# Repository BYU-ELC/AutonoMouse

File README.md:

# AutonoMouse

## Introduction
Lightweight and low cost autonomous robotics platform for students to gain skills and have fun!

There are two version to this project. 

V1's objective is to build a small autonomous car using Arduino Nano as a controller. The car drives forward until sensing an object. When it senses an object it pivots to both sides to find both distances to the nearest object. It then chooses to travel the distance that is greater. 

V2's objective is to build a similiar autonomous car using ESP32 as a controller. However, this version
allow's the user to put the car into remote control mode where the user can control the car via bluetooth
using an Android smartphone. This doesn't work with an IPhone because there are no opensource bluetooth apps 
that in the App Store. 

## V1 Things to Change
More accessibility Linux and Apple users. Document how to download Arduino IDE and how to interfaces with Arduino devices.

## V2 Things to Change
Finish development for V2. Mostly needs work with the servos.

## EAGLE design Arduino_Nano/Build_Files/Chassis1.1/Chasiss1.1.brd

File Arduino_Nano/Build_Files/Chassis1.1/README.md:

Chassis1.1 is a revision of the previous Chassis1.0.

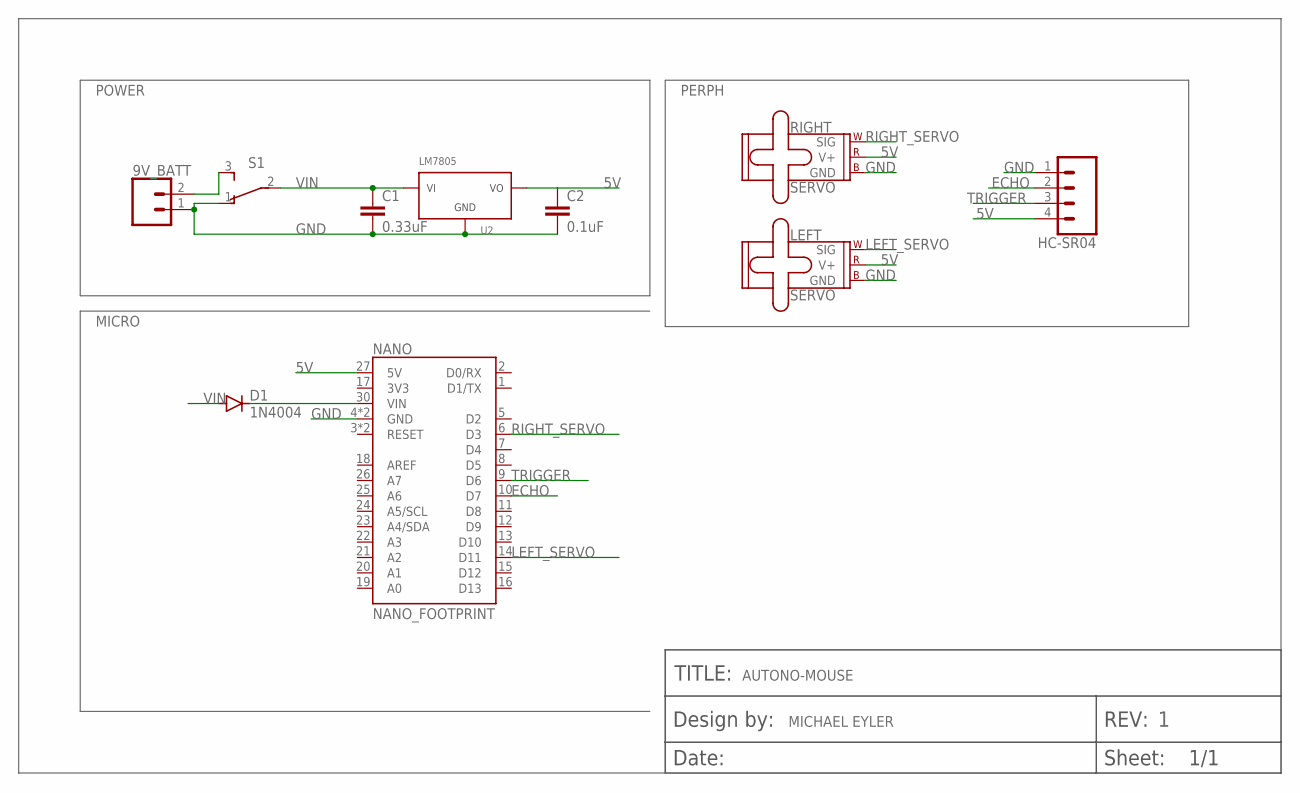
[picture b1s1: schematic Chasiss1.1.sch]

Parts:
9V_BATT: CONN_02; 1X02
C1: 0.33uF; CAP-PTH-SMALL-KIT
C2: 0.1uF; CAP-PTH-SMALL-KIT
D1: 1N4004; DO41-10
HC-SR04: CONN_04PTH; 1X04
LEFT: SERVO; 1X03
NANO: NANO_FOOTPRINT; NANO
RIGHT: SERVO; 1X03
S1: TL36PO; TL3XPO
U2: LM7805; TO220H
U$1: FRAME-BADGE; DUMMY

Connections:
5V: C2.1, HC-SR04.4, LEFT.2 (V+), NANO.27 (5V), RIGHT.2 (V+), U2.3 (VOUT)
ECHO: HC-SR04.2, NANO.10 (D7)
GND: 9V_BATT.1, C1.2, C2.2, HC-SR04.1, LEFT.3 (GND), NANO.4 (GND), NANO.29 (GND), RIGHT.3 (GND), S1.1 (O), U2.2 (GND)
LEFT_SERVO: LEFT.1 (SIG), NANO.14 (D11)
unnamed: 9V_BATT.2, S1.3 (S)
unnamed: D1.C, NANO.30 (VIN)
RIGHT_SERVO: NANO.6 (D3), RIGHT.1 (SIG)
TRIGGER: HC-SR04.3, NANO.9 (D6)
VIN: C1.1, D1.A, S1.2, U2.1 (VIN)

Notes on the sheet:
POWER
PERPH
MICRO
MICHAEL EYLER
AUTONO-MOUSE

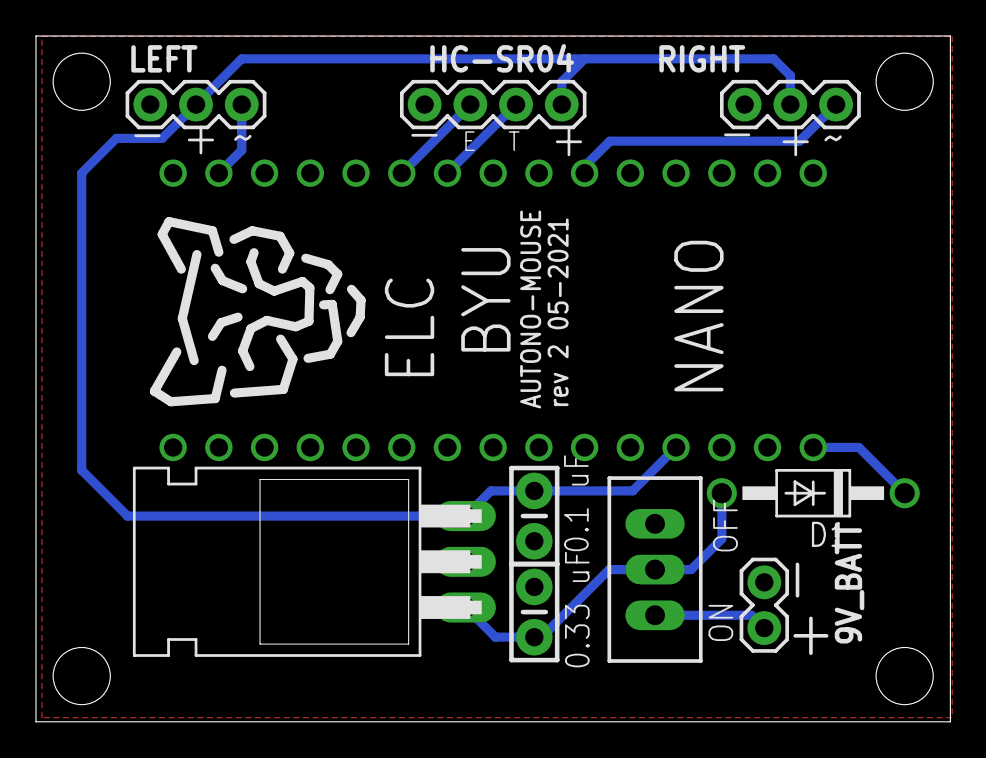
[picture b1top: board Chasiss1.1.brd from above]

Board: 2 copper layers, 50.8 x 38.1 mm, 11 parts (0 on the bottom side), 9 nets.

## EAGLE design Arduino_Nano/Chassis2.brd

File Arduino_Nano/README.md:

# Arduino Nano version of the Autonomouse

## PCB
Recommended: Use gerber files in Build_Files->Chassis1.1->Chasiss1.1_2021-09-01.zip. 

## Acrylic Base
Laser cut the acrylic base using Arduino_Nano_chassis.svg in Build_Files folder. 

## Labs
Follow the labs sequentially in Labs folder.

## Code
Code is provided along with most labs. Upload the code to Arduino Nano using a USB A-Mini and the Arduino IDE.

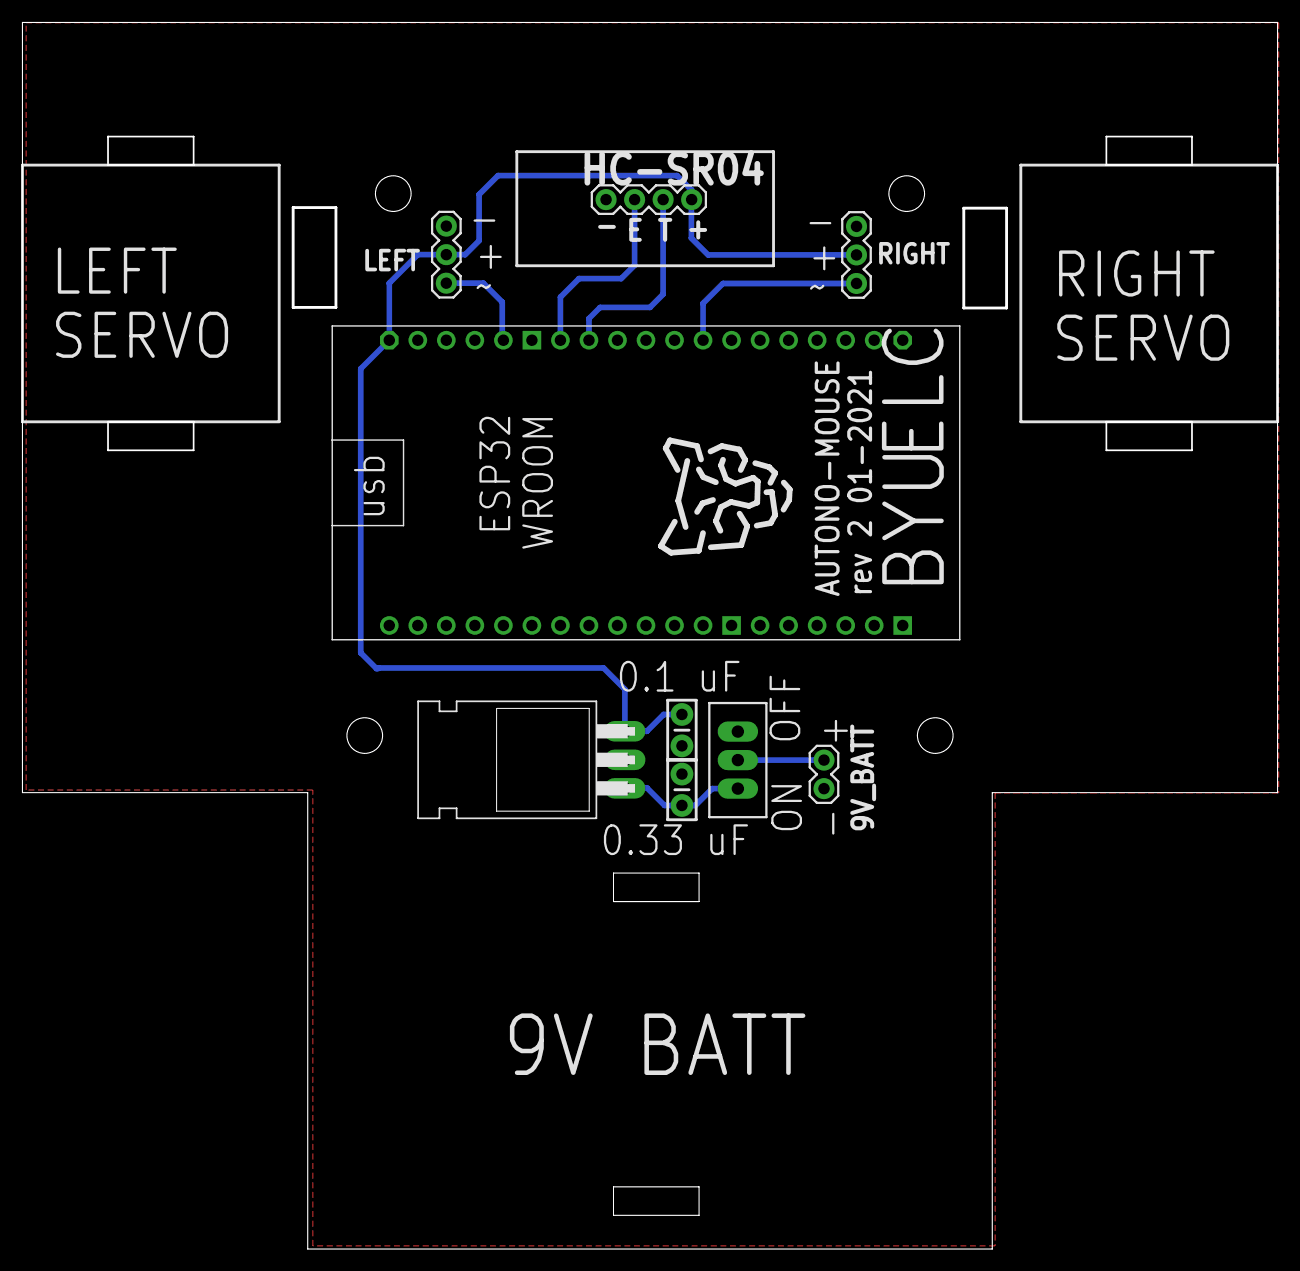
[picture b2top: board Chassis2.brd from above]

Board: 2 copper layers, 111.8 x 109.2 mm, 10 parts (0 on the bottom side), 8 nets.

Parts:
9V_BATT: 1X02
C1: 0.33uF; CAP-PTH-SMALL-KIT
C2: 0.1uF; CAP-PTH-SMALL-KIT
HC-SR04: 1X04
LEFT: SERVO; 1X03
RIGHT: SERVO; 1X03
S1: TL36PO; TL3XPO
U2: LM7805; TO220H
U$1: FRAME-BADGE; DUMMY
U$2: SHOP_ESP; ESP32-WROOM-32

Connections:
5V: C2.1, HC-SR04.4, LEFT.2, RIGHT.2, U2.3, U$2.P$1
ECHO: HC-SR04.2, U$2.P$7
GND: 9V_BATT.1, C1.2, C2.2, HC-SR04.1, LEFT.3, RIGHT.3, U2.2, U$2.P$6, U$2.P$32, U$2.P$38
LEFT_SERVO: LEFT.1, U$2.P$5
unnamed: 9V_BATT.2, S1.2
RIGHT_SERVO: RIGHT.1, U$2.P$12
TRIGGER: HC-SR04.3, U$2.P$8
VIN: C1.1, S1.3, U2.1

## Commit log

2021-06-11 added labs 1,2,3
2021-06-26 Uploaded Arduino labs and code
2021-06-30 updated Arduino labs
2021-07-23 updates to v2 labs
2021-07-23 update to README
2021-07-23 changes to svg templates
2021-08-11 minor changes
2021-08-11 minor grammar fixes
2021-08-12 minor fixes to esp32
2021-08-12 added lab questions
2021-08-12 minor changes to lab0
2021-08-18 Added Pdfs
2021-08-20 Added diode protection board
2021-08-20 updated lab 5 and 6
2021-09-01 Fixed Issue with 3.3v regulator overpowering
2021-09-03 republished lab0
2021-09-04 PCB and base changes
2021-09-07 update to BOM
2021-09-09 updated lab0
2021-09-20 added resistor to BOM
2021-09-27 Reverse diode not needed, routing was done incorrectly by accident. Also added route from voltage regulator to the Arduino Nano for power. Updated some notes in the README and cleaned out some unused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
2021-09-28 fix to power Arduino board
2021-11-19 Added PCB layout PDF
2021-12-14 Halway through editing Lab 0 notes.
2021-12-14 Improved grammer under PCB paragraph.
2021-12-14 no changes
2021-12-14 links are good, typos are filtered out
2021-12-14 working chassis
2021-12-15 typos filtered out, hyperlinks work, page optimization
2021-12-15 Lab 2 typos fixed, hyperlinks work, updated info.
2021-12-15 typos filtered out, hyperlinks work
2021-12-15 fixed typos and minor grammatical errors
2021-12-15 minor grammatical error fix
2021-12-15 Minor typos fixed
2021-12-15 updated pdf
2021-12-15 Updated Lab-1 pdf
2021-12-15 updated lab2 pdf
2021-12-15 Lab 3 pdf updated
2021-12-15 Updated Lab4 pdf
2021-12-15 Updated Lab5 PDF
2021-12-15 Updated Lab6 PDF
2021-12-15 Cleaned up code
2021-12-15 Cleaned up, and fixed code issues
2021-12-15 Cleaned up code and bugs
2021-12-15 Code cleaned up and comments added for user learning
2021-12-15 edited in branch for lab 6... several typos and grammatical errors
2022-01-06 updated PCB sizes
2022-01-11 updated PCB photo for reference
2022-02-08 updated wrong pwm pin
2022-02-15 updated 11 and 12 pin error to 6 and 7
2022-10-31 Add JLC PCB Files
2022-10-31 Rename JLC zip file
2023-09-14 Changed links in lab instructions

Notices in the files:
parts and their libraries:
SparkFun-Connectors: Licensing: Creative Commons ShareAlike 4.0 International - https://creativecommons.org/licenses/by-sa/4.0
